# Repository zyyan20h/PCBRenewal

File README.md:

# PCB Renewal
PCB Renewal is a sustainable fabrication technique that enables renewal and reconfiguration of obsolete PCBs. This is an accompanying repository of a [research paper](https://doi.org/10.1145/3706598.3714276) published in ACM CHI 2025.

## KiCad Plugin
A plugin for the circuit design software, KiCad, that facilitates this reconfiguring process. It can be used to compare two circuit designs, crosschecking the traces and pads to figure out an efficient way to remove certain traces to transform one circuit into another.

### Installation

##### 1. Open your KiCad Plugin Directory
* You can do this by opening the PCB Editor and clicking on **Tools** > **External Plugins** > **Open Plugin Directory**
* This should open the file location where plugins are stored

##### 2. Copy plugin files into the directory
* Copy the **renewal_plugin** folder from the repository and paste it into the plugin directory
* Make sure to copy the entire folder, not just its contents

##### 3. Install Dependencies
* This plugin uses the **shapely** package
* KiCad has its own python installation, so the dependency must be intalled even if you have the package on your system's python
* Open the **KiCad 7.0 Command Prompt** (a different application from KiCad)
* type `pip install shapely` and press enter

##### 4. Check if plugin works
* Click on **Tools** > **External Plugins** > **Refresh Plugins**
* You should see the plugin show up at the right of the toolbar (the one at the top)
* Click on the plugin icon to use it

### Troubleshooting
If you don't see the plugin, make sure that you:
* Can see the plugin folder when you open the Plugin Directory
* Have installed **shapely** on *KiCad's installation of python* (see step 3)
* Have refreshed the plugins (see step 4)

One other thing you can try is using the **Python Scripting Console**
* Click the button with the terminal icon at the top of the screen
* Type `import pcbnew` and press enter
* Type `print(pcbnew.FULL_BACK_TRACE)` and press enter
* The error message should be shown on the screen
* Report the error message to the developer

### Version Information
* KiCad: 7.0.10
* Python: 3.9.16
* numpy: 1.26.1
* shapely: 2.0.4
* wxPython: 4.2.1

## Examples
Various circuit board designs that were used and reconfigured into other designs, e.g turning a PCB for a watch into one for a cat toy.

## Archive
Arudino code and old examples used during the project development.

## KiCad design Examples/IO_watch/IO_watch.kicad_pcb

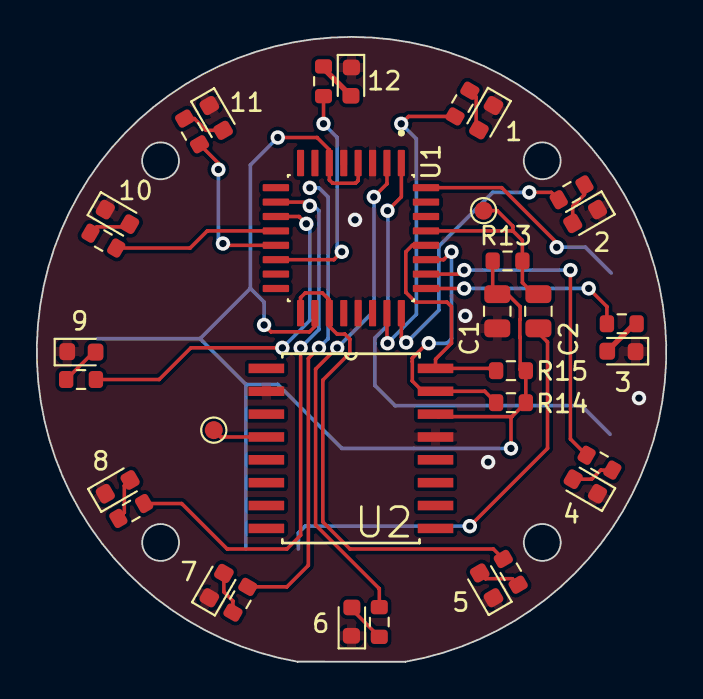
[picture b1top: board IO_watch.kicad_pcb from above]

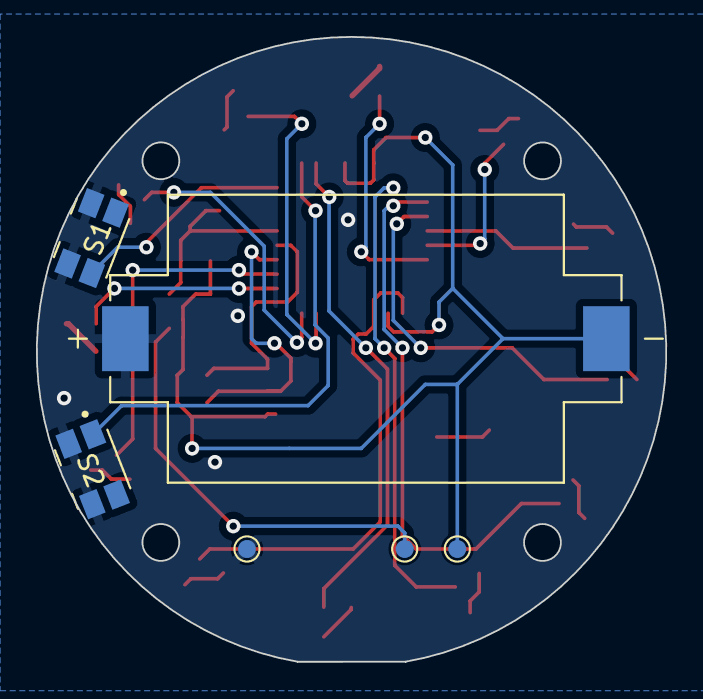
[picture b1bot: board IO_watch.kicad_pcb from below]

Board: 2 copper layers, 35.0 x 34.7 mm, 39 parts (6 on the bottom side), 33 nets.

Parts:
1, 2, 3, 4, 5, 12: LED; LED_0603_1608Metric
BT1: 1060TR; BAT_1060TR
C1: 1uF; C_0805_2012Metric
C2: 0.1uF; C_0805_2012Metric
D6, D7, D8, D9, D10, D11: LED; LED_0603_1608Metric
R1, R2, R3, R4, R5, R6, R7, R8, R9, R10, R11, R12: R; R_0603_1608Metric
R13, R14, R15: 10K; R_0603_1608Metric
S1, S2: EVQ-P7A01P; SW_EVQ-P7A01P
TP1, TP2, TP5, TP6, TP7: TestPoint; TestPoint_Pad_D1.0mm
U1: ATMEGA328P-AU; atmega328P_shinked
U2: DS3231S; DS3231

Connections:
/A0: R1.2, U1.23 (PC0)
/A1: R2.2, U1.24 (PC1)
/A2: R3.2, U1.25 (PC2)
/A3: R4.2, U1.26 (PC3)
/D2: S1.1_1, S1.1_2, U1.32 (PD2)
/D3: S2.1_1, S2.1_2, U1.1 (PD3)
/D4: R6.2, U1.2 (PD4)
/D5: R7.2, U1.9 (PD5)
/D6: R8.2, U1.10 (PD6)
/D7: R9.2, U1.11 (PD7)
/D8: R10.2, U1.12 (PB0)
/D9: R11.2, U1.13 (PB1)
/D10: R12.2, U1.14 (PB2)
/D13: R5.2, U1.17 (PB5), U1.19 (ADC6)
/D-: C2.2, TP2.1
/RST: C2.1, R13.1, TP7.1, U1.29 (PC6/~RESET)
/SCL: R15.1, U1.28 (PC5), U2.16 (SCL)
/SDA: R14.2, U1.27 (PC4), U2.15 (SDA)
GND: 1.1 (K), 2.1 (K), 3.1 (K), 4.1 (K), 5.1 (K), 12.1 (K), BT1.P, C1.2, D6.1 (K), D7.1 (K), D8.1 (K), D9.1 (K), D10.1 (K), D11.1 (K), S1.2_1, S1.2_2, S2.2_1, S2.2_2, TP5.1, U1.3 (GND), U1.5 (GND), U1.21 (GND), U2.2 (VCC), U2.13 (GND)
unnamed: 1.2 (A), R1.1
unnamed: 2.2 (A), R2.1
unnamed: 3.2 (A), R3.1
unnamed: 4.2 (A), R4.1
unnamed: 5.2 (A), R5.1
unnamed: D6.2 (A), R6.1
unnamed: D7.2 (A), R7.1
unnamed: D8.2 (A), R8.1
unnamed: D9.2 (A), R9.1
unnamed: D10.2 (A), R10.1
unnamed: D11.2 (A), R11.1
unnamed: 12.2 (A), R12.1
unnamed: TP6.1, U2.4 (~RST)
VCC: BT1.N, C1.1, R13.2, R14.1, R15.2, TP1.1, U1.4 (VCC), U1.6 (VCC), U1.18 (AVCC), U2.14 (VBAT)

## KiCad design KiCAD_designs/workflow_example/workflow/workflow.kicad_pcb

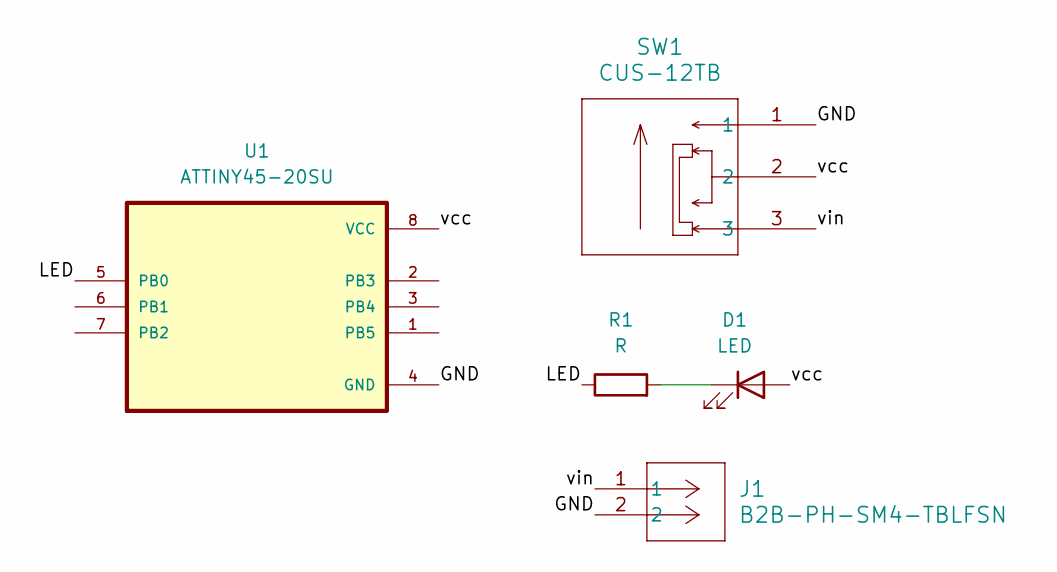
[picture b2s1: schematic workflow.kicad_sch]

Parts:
D1: LED; LED_1206_3216Metric
J1: B2B-PH-SM4-TBLFSN; B2B-PH-SM4-TBLFSN_JST
R1: R; R_0805_2012Metric
SW1: CUS-12TB; CUS-12TB_NDC
U1: ATTINY45-20SU; SOIC127P794X202-8N

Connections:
/GND: J1.2, SW1.1, U1.4 (GND)
/LED: R1.1, U1.5 (PB0)
/vcc: D1.2 (A), SW1.2, U1.8 (VCC)
/vin: J1.1, SW1.3
unnamed: D1.1 (K), R1.2

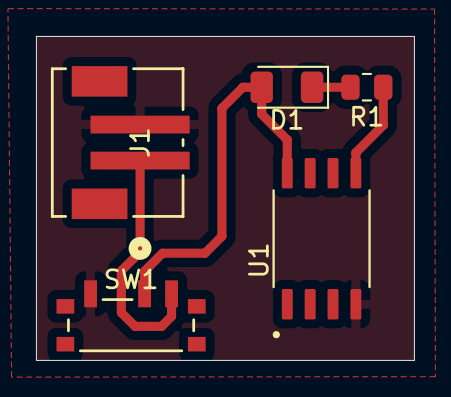
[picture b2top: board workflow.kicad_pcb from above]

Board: 2 copper layers, 21.0 x 18.0 mm, 5 parts (0 on the bottom side), 5 nets.

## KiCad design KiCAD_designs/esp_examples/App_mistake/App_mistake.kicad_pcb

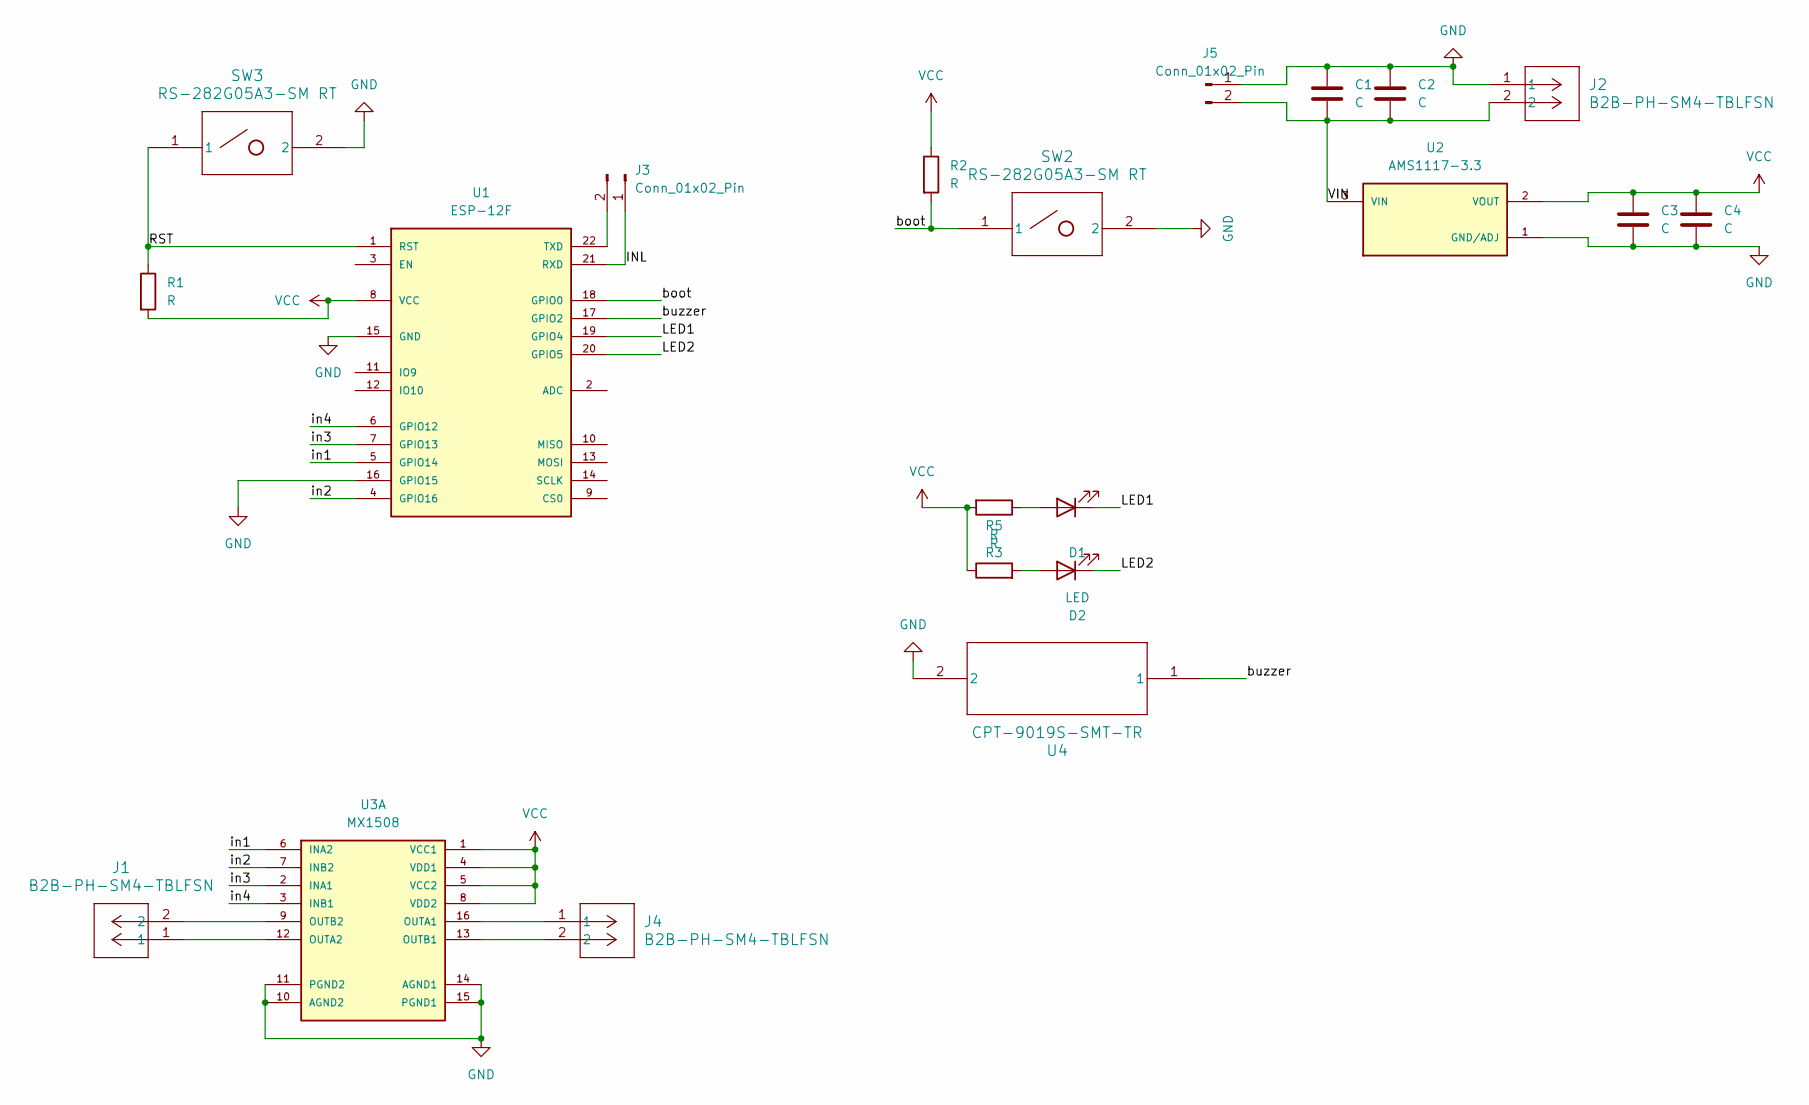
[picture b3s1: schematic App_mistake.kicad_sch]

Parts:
C1, C2, C3, C4: C; C_0805_2012Metric
D1, D2: LED; LED_1206_3216Metric
J1, J2, J4: B2B-PH-SM4-TBLFSN; B2B-PH-SM4-TBLFSN_JST
J3, J5: Conn_01x02_Pin; PinHeader_1x02_P2.54mm_Vertical
R1, R2, R3, R5: R; R_0805_2012Metric
SW2, SW3: RS-282G05A3-SM RT; RS-282G05A3-SM RT_CNK
U1: ESP-12F
U2: AMS1117-3.3; SOT229P700X180-4N
U3: MX1508
U4: CPT-9019S-SMT-TR; SM_CPT_9X9_CUD

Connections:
/INL: J3.1, U1.21 (RXD)
/LED1: D1.1 (K), U1.19 (GPIO4)
/LED2: D2.1 (K), U1.20 (GPIO5)
/RST: R1.1, SW3.1, U1.1 (RST)
/VIN: C1.2, C2.2, J2.2, J5.2, U2.3 (VIN)
/boot: R2.2, SW2.1, U1.18 (GPIO0)
/buzzer: U1.17 (GPIO2), U4.1
/in1: U1.5 (GPIO14), U3.6 (INA2)
/in2: U1.4 (GPIO16), U3.7 (INB2)
/in3: U1.7 (GPIO13), U3.2 (INA1)
/in4: U1.6 (GPIO12), U3.3 (INB1)
GND: C1.1, C2.1, C3.2, C4.2, J2.1, J5.1, SW2.2, SW3.2, U1.15 (GND), U1.16 (GPIO15), U2.1 (GND/ADJ), U3.10 (AGND2), U3.11 (PGND2), U3.14 (AGND1), U3.15 (PGND1), U4.2
unnamed: D1.2 (A), R3.1
unnamed: D2.2 (A), R5.2
unnamed: J3.2, U1.22 (TXD)
unnamed: J4.1, U3.16 (OUTA1)
unnamed: J1.1, U3.12 (OUTA2)
unnamed: J4.2, U3.13 (OUTB1)
unnamed: J1.2, U3.9 (OUTB2)
VCC: C3.1, C4.1, R1.2, R2.1, R3.2, R5.1, U1.8 (VCC), U2.2 (VOUT), U3.1 (VCC1), U3.4 (VDD1), U3.5 (VCC2), U3.8 (VDD2)

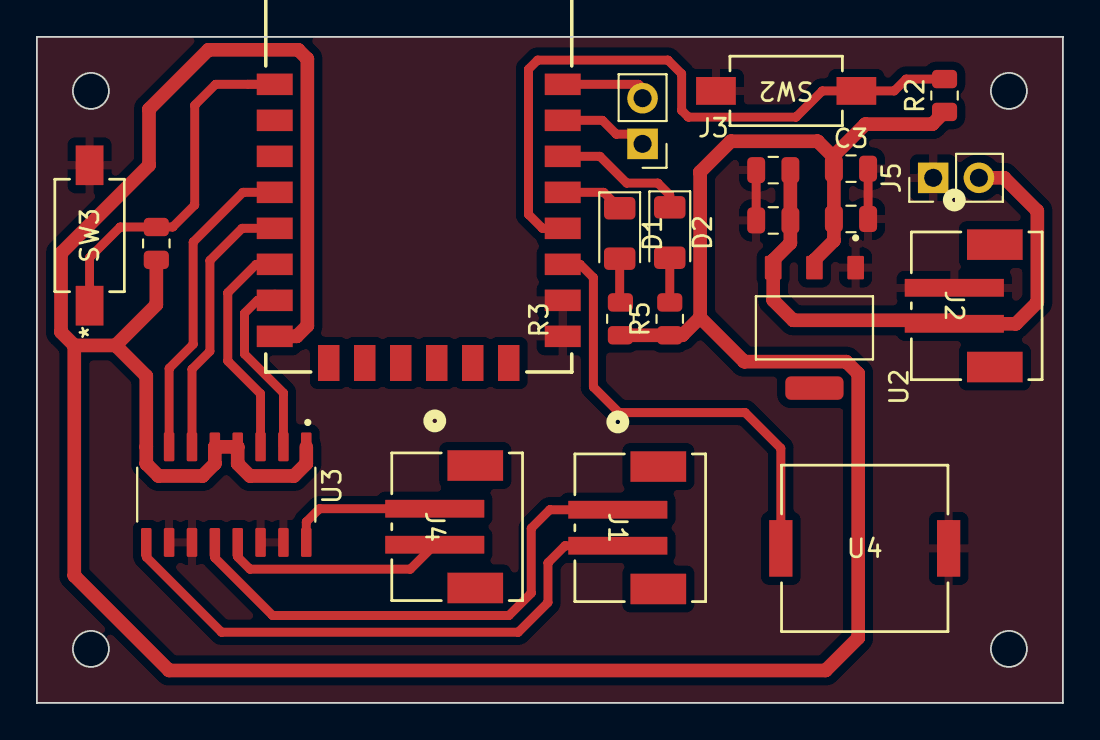
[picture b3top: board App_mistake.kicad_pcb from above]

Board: 2 copper layers, 57.0 x 37.0 mm, 21 parts (0 on the bottom side), 20 nets.

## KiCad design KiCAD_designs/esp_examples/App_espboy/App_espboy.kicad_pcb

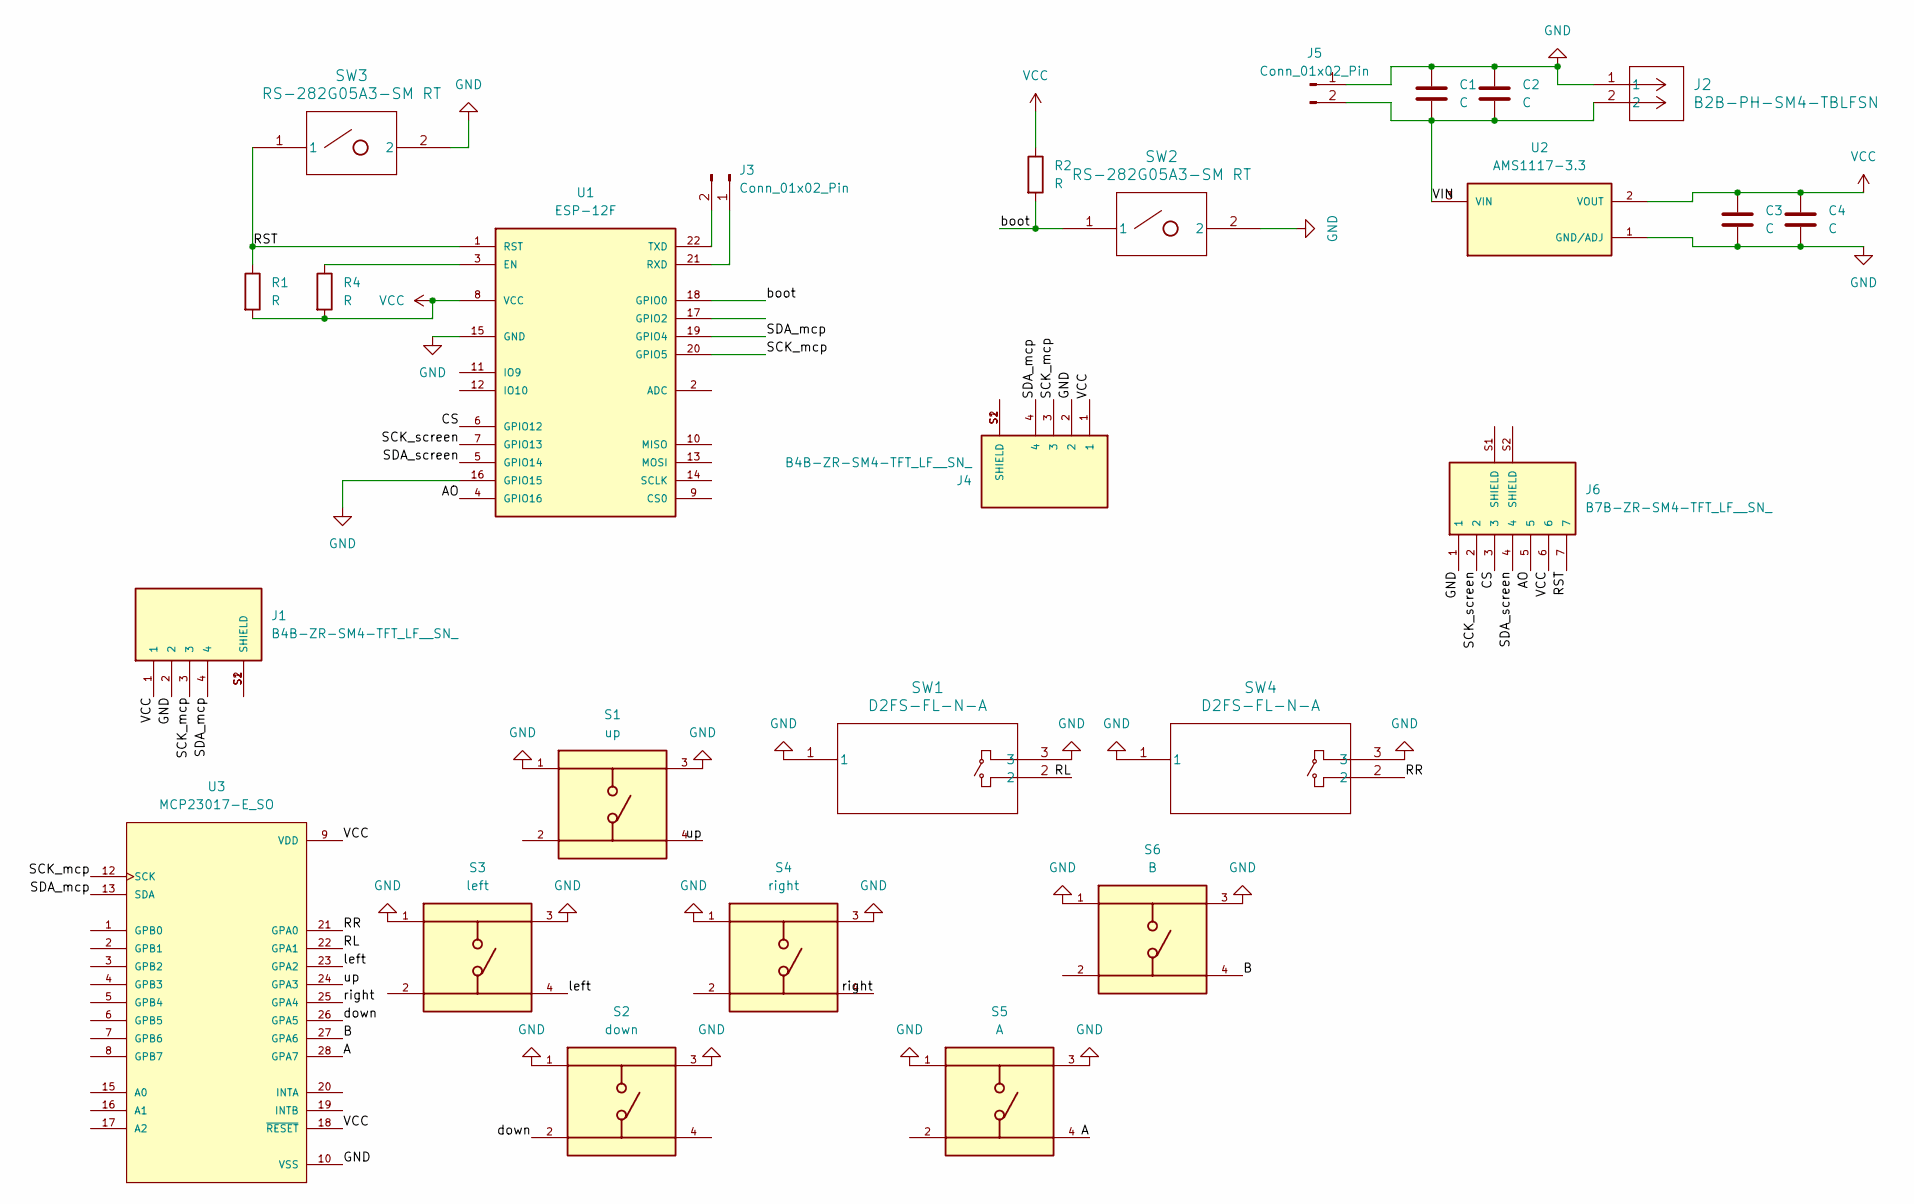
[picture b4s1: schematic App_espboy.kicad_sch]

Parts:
C1, C2, C3, C4: C; C_0805_2012Metric
J1, J4: B4B-ZR-SM4-TFT_LF__SN_; JST_B4B-ZR-SM4-TFT_LF__SN_
J2: B2B-PH-SM4-TBLFSN; B2B-PH-SM4-TBLFSN_JST
J3, J5: Conn_01x02_Pin; PinHeader_1x02_P2.54mm_Vertical
J6: B7B-ZR-SM4-TFT_LF__SN_; B7B-ZR-SM4-TBLFSN_JST
R1, R2, R4: R; R_0805_2012Metric
S1: up; switch_6
S2: down; switch_6
S3: left; switch_6
S4: right; switch_6
S5: A; switch_6
S6: B; switch_6
SW1, SW4: D2FS-FL-N-A; D2FS-FL-N-A_OMR
SW2, SW3: RS-282G05A3-SM RT; RS-282G05A3-SM RT_CNK
U1: ESP-12F
U2: AMS1117-3.3; SOT229P700X180-4N
U3: MCP23017-E_SO; MCP23017

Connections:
/A: S5.4, U3.28 (GPA7)
/AO: J6.5, U1.4 (GPIO16)
/B: S6.4, U3.27 (GPA6)
/CS: J6.3, U1.6 (GPIO12)
/RL: SW1.2, U3.22 (GPA1)
/RR: SW4.2, U3.21 (GPA0)
/RST: J6.7, R1.1, SW3.1, U1.1 (RST)
/SCK_mcp: J1.3, J4.3, U1.20 (GPIO5), U3.12 (SCK)
/SCK_screen: J6.2, U1.7 (GPIO13)
/SDA_mcp: J1.4, J4.4, U1.19 (GPIO4), U3.13 (SDA)
/SDA_screen: J6.4, U1.5 (GPIO14)
/VIN: C1.2, C2.2, J2.2, J5.2, U2.3 (VIN)
/boot: R2.2, SW2.1, U1.18 (GPIO0)
/down: S2.2, U3.26 (GPA5)
/left: S3.4, U3.23 (GPA2)
/right: S4.4, U3.25 (GPA4)
/up: S1.4, U3.24 (GPA3)
GND: C1.1, C2.1, C3.2, C4.2, J1.2, J2.1, J4.2, J5.1, J6.1, S1.1, S1.3, S2.1, S2.3, S3.1, S3.3, S4.1, S4.3, S5.1, S5.3, S6.1, S6.3, SW1.1, SW1.3, SW2.2, SW3.2, SW4.1, SW4.3, U1.15 (GND), U1.16 (GPIO15), U2.1 (GND/ADJ), U3.10 (VSS)
unnamed: J1.S1 (SHIELD), J1.S2 (SHIELD)
unnamed: J3.1, U1.21 (RXD)
unnamed: J3.2, U1.22 (TXD)
unnamed: J4.S1 (SHIELD), J4.S2 (SHIELD)
unnamed: R4.1, U1.3 (EN)
VCC: C3.1, C4.1, J1.1, J4.1, J6.6, R1.2, R2.1, R4.2, U1.8 (VCC), U2.2 (VOUT), U3.9 (VDD), U3.18 (~RESET)

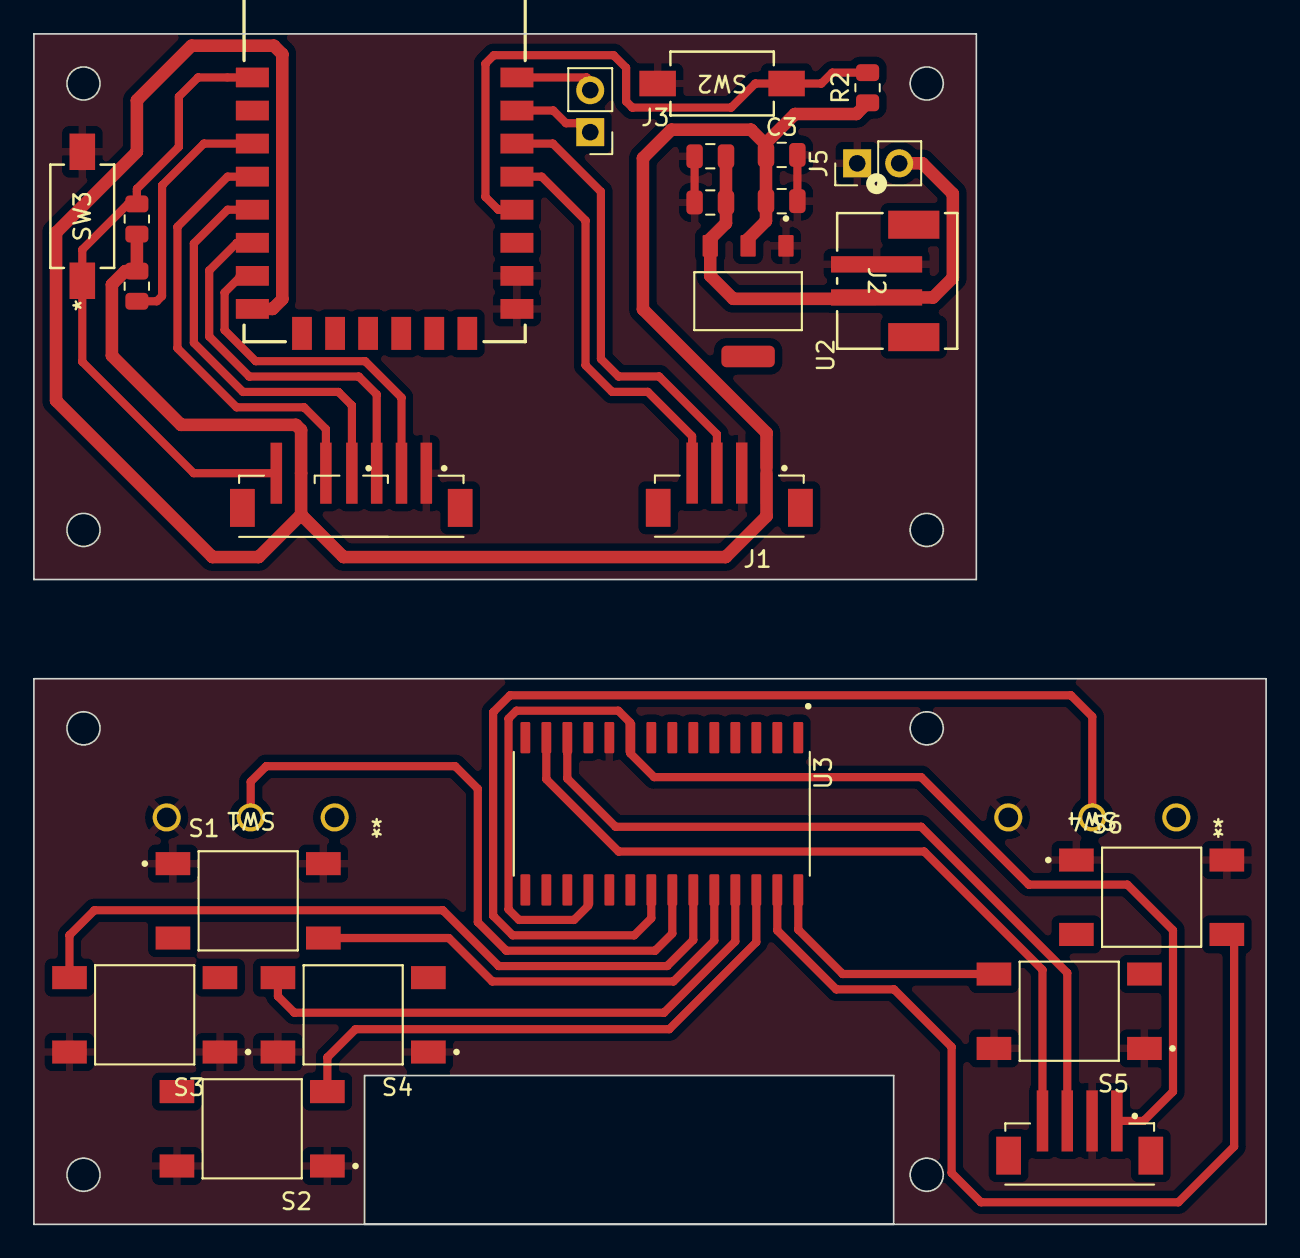
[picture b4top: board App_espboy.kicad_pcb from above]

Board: 2 copper layers, 74.5 x 72.0 mm, 26 parts (0 on the bottom side), 24 nets.

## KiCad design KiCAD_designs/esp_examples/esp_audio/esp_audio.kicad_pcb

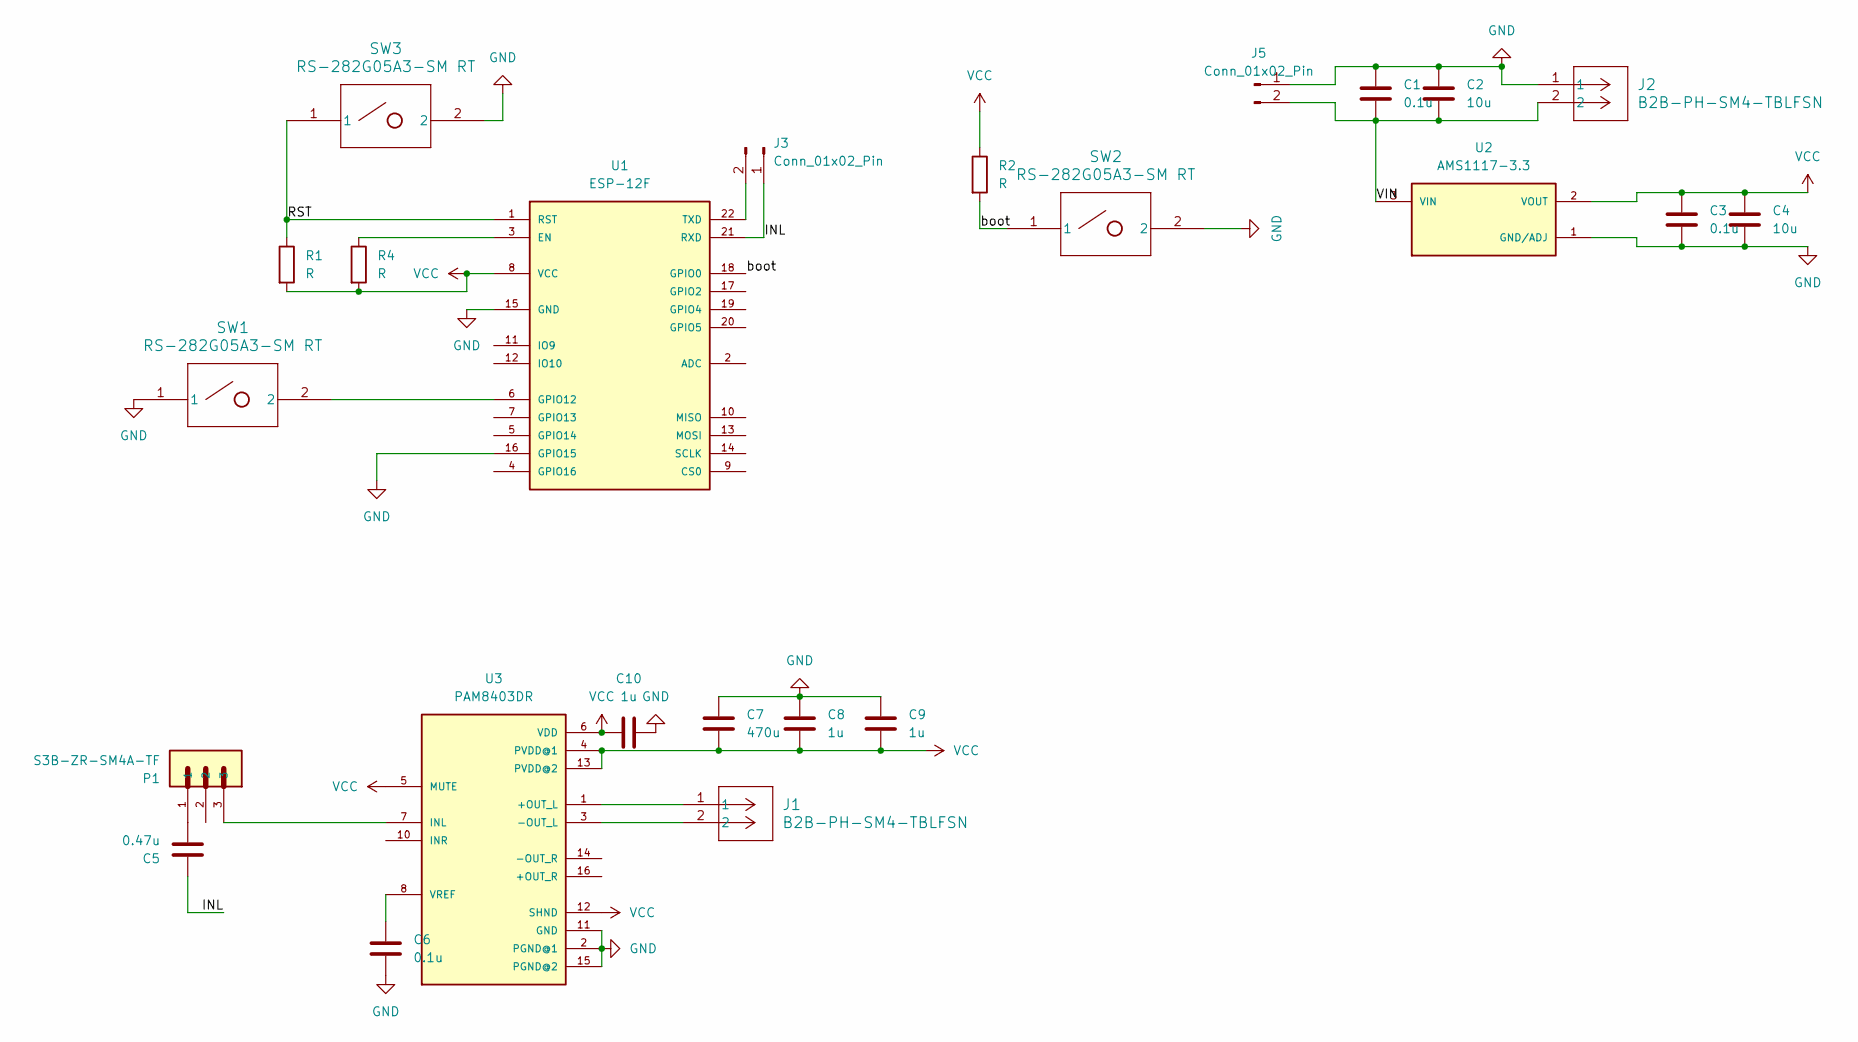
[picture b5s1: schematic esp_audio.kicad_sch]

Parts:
C1, C3, C6: 0.1u; C_0805_2012Metric
C2, C4: 10u; C_0805_2012Metric
C5: 0.47u; C_0805_2012Metric
C7: 470u; CAP_EEEFP1C471AL
C8, C9, C10: 1u; C_0805_2012Metric
J1, J2: B2B-PH-SM4-TBLFSN; B2B-PH-SM4-TBLFSN_JST
J3, J5: Conn_01x02_Pin; PinHeader_1x02_P2.54mm_Vertical
P1: S3B-ZR-SM4A-TF; JST_S3B-ZR-SM4A-TF
R1, R2, R4: R; R_0805_2012Metric
SW1, SW2, SW3: RS-282G05A3-SM RT; RS-282G05A3-SM RT_CNK
U1: ESP-12F
U2: AMS1117-3.3; SOT229P700X180-4N
U3: PAM8403DR; PAM8403

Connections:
/INL: C5.1, J3.1, U1.21 (RXD)
/RST: R1.1, SW3.1, U1.1 (RST)
/VIN: C1.2, C2.2, J2.2, J5.2, U2.3 (VIN)
/boot: R2.2, SW2.1, U1.18 (GPIO0)
GND: C1.1, C2.1, C3.2, C4.2, C6.2, C7.1, C8.1, C9.1, C10.2, J2.1, J5.1, SW1.1, SW2.2, SW3.2, U1.15 (GND), U1.16 (GPIO15), U2.1 (GND/ADJ), U3.2 (PGND@1), U3.11 (GND), U3.15 (PGND@2)
unnamed: C5.2, P1.1
unnamed: J3.2, U1.22 (TXD)
unnamed: R4.1, U1.3 (EN)
unnamed: SW1.2, U1.6 (GPIO12)
unnamed: J1.1, U3.1 (+OUT_L)
unnamed: J1.2, U3.3 (-OUT_L)
unnamed: P1.3, U3.7 (INL)
unnamed: C6.1, U3.8 (VREF)
VCC: C3.1, C4.1, C7.2, C8.2, C9.2, C10.1, R1.2, R2.1, R4.2, U1.8 (VCC), U2.2 (VOUT), U3.4 (PVDD@1), U3.5 (MUTE), U3.6 (VDD), U3.12 (SHND), U3.13 (PVDD@2)

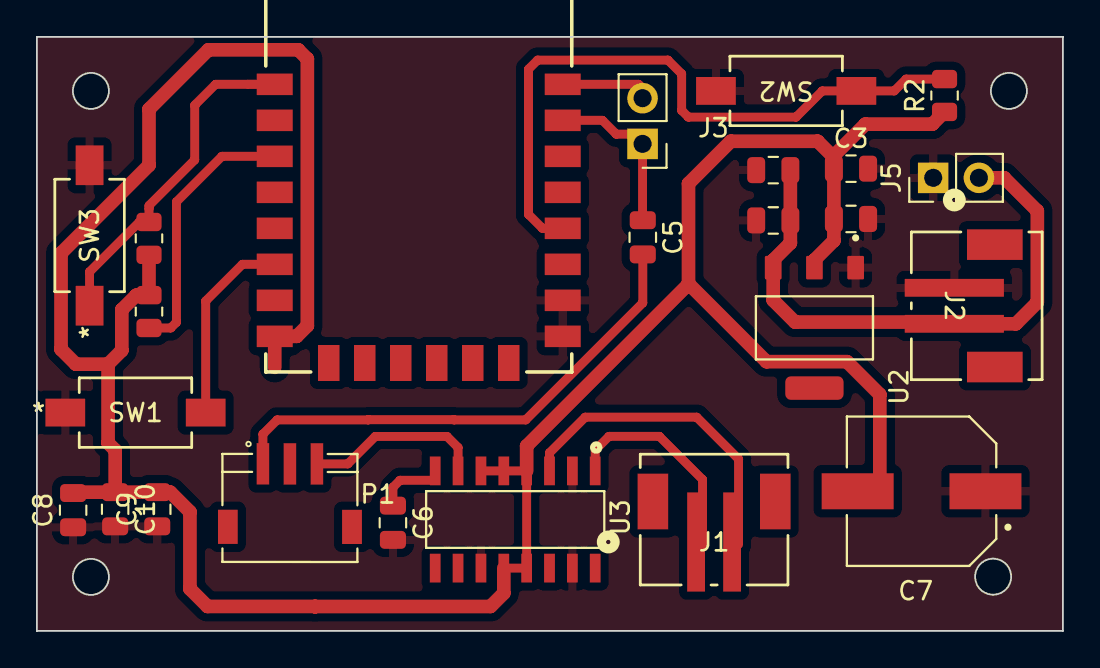
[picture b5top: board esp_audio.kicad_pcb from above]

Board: 2 copper layers, 57.0 x 33.0 mm, 24 parts (0 on the bottom side), 14 nets.

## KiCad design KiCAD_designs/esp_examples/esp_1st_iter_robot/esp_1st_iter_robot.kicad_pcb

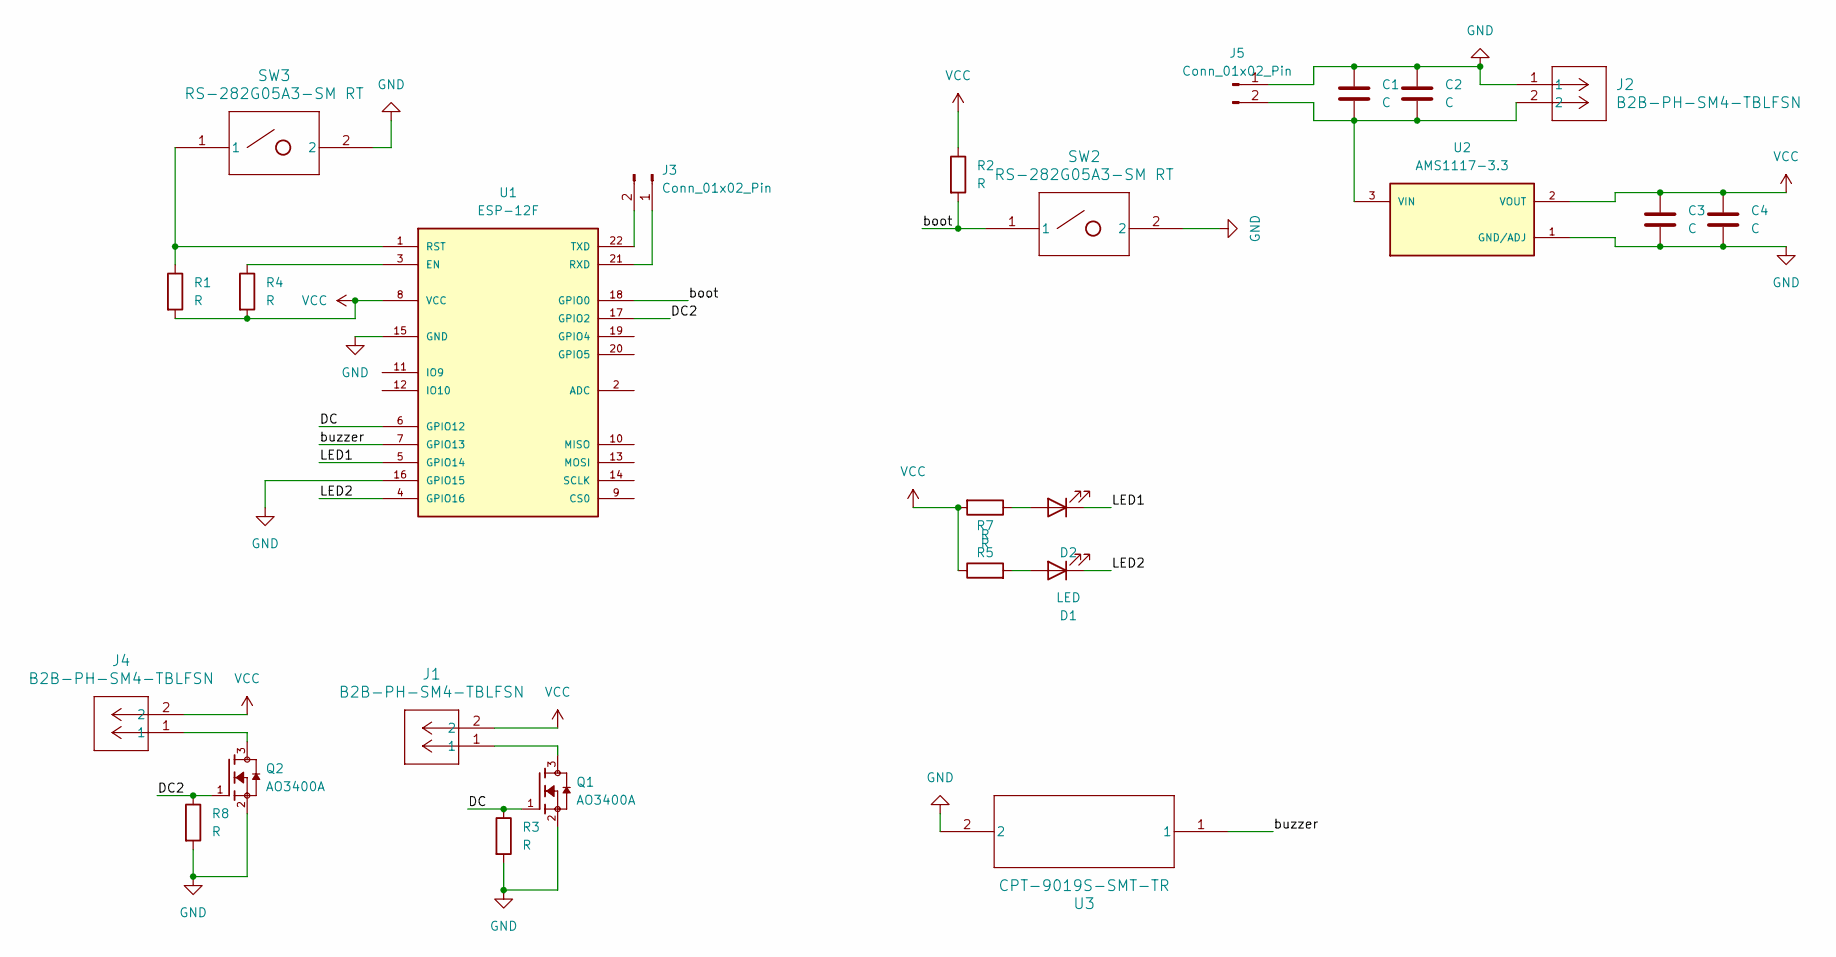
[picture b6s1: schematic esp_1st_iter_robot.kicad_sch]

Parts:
C1, C2, C3, C4: C; C_0805_2012Metric
D1, D2: LED; LED_1206_3216Metric
J1, J2, J4: B2B-PH-SM4-TBLFSN; CONN_B2B-PH-SM4-TBLFSN_JST
J3, J5: Conn_01x02_Pin; PinHeader_1x02_P2.54mm_Vertical
Q1, Q2: AO3400A; SOT95P280X125-3N; PARTREV L
R1, R2, R3, R4, R5, R7, R8: R; R_0805_2012Metric
SW2, SW3: RS-282G05A3-SM RT; RS-282G05A3-SM RT_CNK
U1: ESP-12F
U2: AMS1117-3.3; SOT229P700X180-4N
U3: CPT-9019S-SMT-TR; SM_CPT_9X9_CUD

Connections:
/DC: Q1.1, R3.1, U1.6 (GPIO12)
/DC2: Q2.1, R8.1, U1.17 (GPIO2)
/LED1: D2.1 (K), U1.5 (GPIO14)
/LED2: D1.1 (K), U1.4 (GPIO16)
/boot: R2.2, SW2.1, U1.18 (GPIO0)
/buzzer: U1.7 (GPIO13), U3.1
GND: C1.1, C2.1, C3.2, C4.2, J2.1, J5.1, Q1.2, Q2.2, R3.2, R8.2, SW2.2, SW3.2, U1.15 (GND), U1.16 (GPIO15), U2.1 (GND/ADJ), U3.2
unnamed: D1.2 (A), R7.2
unnamed: D2.2 (A), R5.1
unnamed: J1.1, Q1.3
unnamed: J3.1, U1.21 (RXD)
unnamed: J3.2, U1.22 (TXD)
unnamed: J4.1, Q2.3
unnamed: C1.2, C2.2, J2.2, J5.2, U2.3 (VIN)
unnamed: R4.1, U1.3 (EN)
unnamed: R1.1, SW3.1, U1.1 (RST)
VCC: C3.1, C4.1, J1.2, J4.2, R1.2, R2.1, R4.2, R5.2, R7.1, U1.8 (VCC), U2.2 (VOUT)

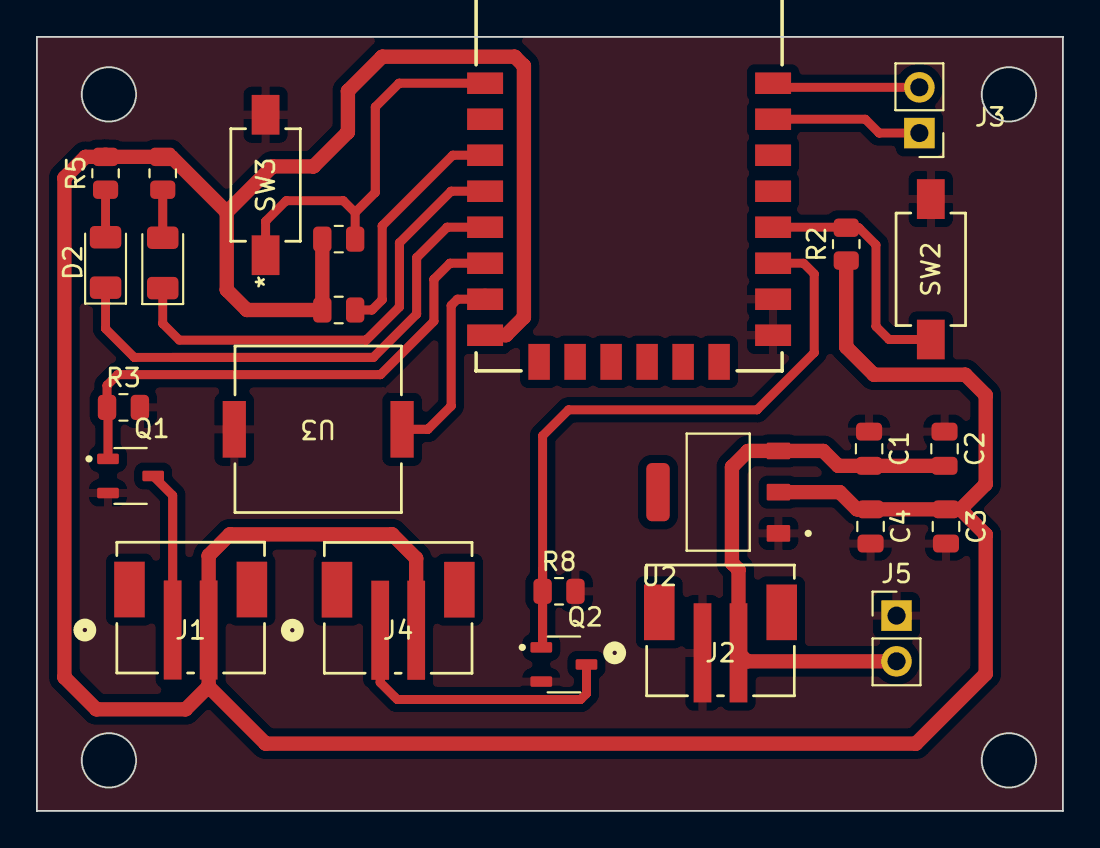
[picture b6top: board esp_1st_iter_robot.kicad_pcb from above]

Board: 2 copper layers, 57.0 x 43.0 mm, 25 parts (0 on the bottom side), 17 nets.

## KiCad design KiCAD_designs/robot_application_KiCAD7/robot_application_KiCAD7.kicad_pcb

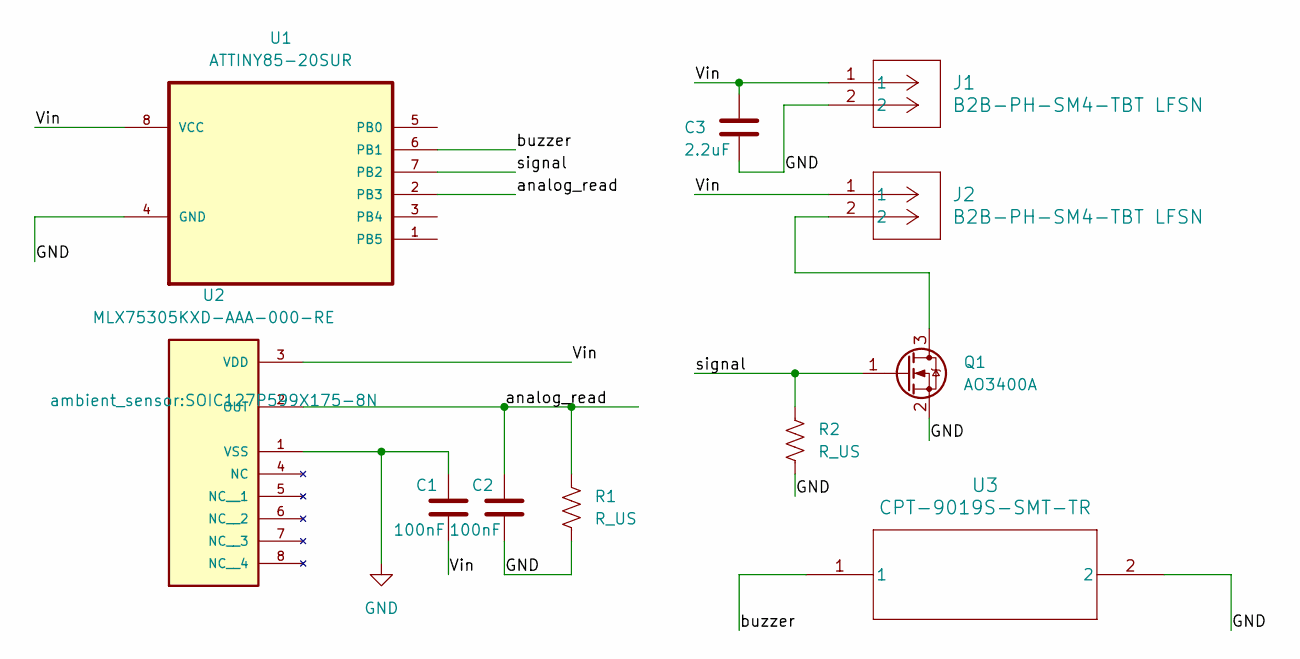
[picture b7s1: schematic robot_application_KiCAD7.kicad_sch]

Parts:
C1, C2: 100nF; C_0805_2012Metric
C3: 2.2uF; C_0805_2012Metric
J1, J2: B2B-PH-SM4-TBT LFSN; CONN2_B2B-PH-SM4_JST
Q1: AO3400A; SOT-23
R1, R2: R_US; R_0805_2012Metric
U1: ATTINY85-20SUR; MPN ATTINY85-20SUR
U2: MLX75305KXD-AAA-000-RE; SOIC127P599X175-8N; PARTREV REVISION 9 - OCTOBER 17, 2016
U3: CPT-9019S-SMT-TR; SM_CPT_9X9_CUD

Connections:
/Vin: C1.2, C3.1, J1.1, J2.1, U1.8 (VCC), U2.3 (VDD)
/analog_read: C2.1, R1.1, U1.2 (PB3), U2.2 (OUT)
/buzzer: U1.6 (PB1), U3.1
/signal: Q1.1 (G), R2.1, U1.7 (PB2)
GND: C1.1, C2.2, C3.2, J1.2, Q1.2 (S), R1.2, R2.2, U1.4 (GND), U2.1 (VSS), U3.2
unnamed: J2.2, Q1.3 (D)

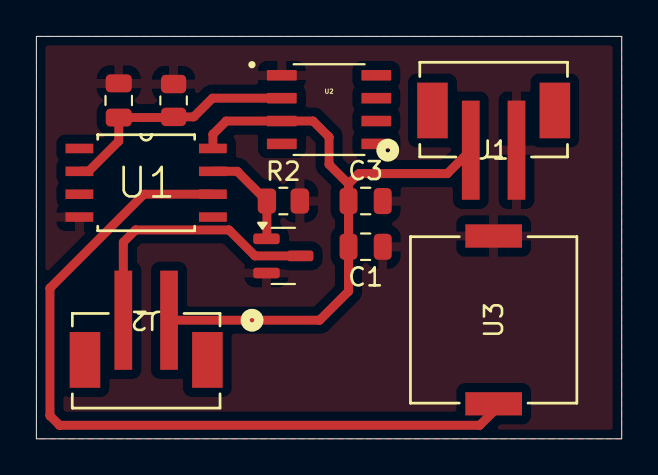
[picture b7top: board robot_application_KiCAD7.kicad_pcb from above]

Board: 2 copper layers, 32.5 x 22.4 mm, 11 parts (0 on the bottom side), 6 nets.

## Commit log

2024-01-30 project
2024-02-18 initial plugin commit
2024-02-19 plugin2-_19_24
2024-02-25 Added gerber plotting
2024-03-26 Updated UI
2024-03-26 JS_application_KiCAD_files
    Add new KiCAD files of application
2024-03-26 js_update
2024-03-26 kicad7
2024-03-28 tiny_versions
2024-03-29 esp v1
2024-03-29 esp_bot_fullRoute
2024-03-29 esp_v3_routed with keep-out
2024-03-30 all_iterations initial
2024-04-02 Made the comparison board show after pressing ok, Disabled unnecessary layers in the comparison board
2024-06-10 added svg stuff
2024-06-19 esp_camRoller
2024-06-28 Add files via upload
    8266 application code back up
2024-06-28 Added Arduino testing files. Espboy works
2024-06-29 add datasheets
2024-07-01 cs pin changed to 8266 io12
2024-07-01 cam_roller_redesign
2024-07-03 espboy_full
2024-07-03 espboy_copy
2024-07-08 add 8266 wifi radio code
2024-07-09 audio
2024-07-10 semi working version
2024-07-10 design-cleanup
2024-07-12 button changed
2024-07-12 cs pin 12, add info in README.MD
2024-07-22 Way to select components on board
2024-07-25 Added display window
2024-07-25 larger button boy
2024-07-31 23017
2024-07-31 23017 Updated
2024-08-05 fixed corner alignment
2024-08-09 cam_roller_arduino
2024-08-09 camera_roller_dynamic
2024-08-12 esp design reorg
2024-08-15 UI mistake cam_roller
2024-08-16 Made the exported svgs polygons as opposed to strokes, Layers are now ordered in the UI board visualisation, i.e. F.Cu always appears on front, the original coppers appear in front of the comparisons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
2024-08-16 Removed references to the selection dialog, because it was removed and is causing errors
2024-08-20 offset to 0.45
2024-08-20 workflow example
2024-08-22 Exporting edge cut difference, overwrite stuff
2024-08-22 js 0822
2024-08-26 Fixed bug where edge cuts weren't properly compared after alignment. Made the comparison take into account the current alignment offset
2024-08-26 The components and edge cuts were misaligned when exporting whenever they were aligned for comparison. I offset the components by the alignment offset as well.
2024-08-28 tiles
2024-09-03 implemented the sustainability calculations save for the fr4 material ones. Also I'm using a fixed path length instead of getting it
2024-09-04 added sustainability calculation for fiberglass and copper
2024-09-06 Added functionality to save parameters to the configuration file
2024-09-07 Added labels for the multiple choice boxes in the ALign Boards section
2024-09-08 Made the board visualisation take up the entire right half of the screen
2024-09-08 misalign
2024-09-08 Fixed bug where the edge cuts weren't aligned after comparison
2024-09-10 updated the formulas
2024-09-10 Added ceiling functions to time formulas. Removed comparison method selection and export original board checkbox
2024-09-10 Addeed extra stuff to sustainability evaluation
2024-09-11 fixed some of the sustainability formulas
2024-09-11 calculation final
2024-09-11 Made default sustainability params match the ones in the config file. Labeled the comparison results in the layer controls of the board visualisation
2024-11-11 double layer examples
2024-11-18 ordered
2024-11-22 Added support for vias
2024-11-24 Made pads takes their layer from their parent footprint
2024-12-02 Added 0.1 offset to diameter of drilled out vias
2024-12-02 fixed type error in previous commit
2024-12-03 changed cat ball via size
2024-12-03 Exported edge cuts gerber now includes vias present on the new board and not on the old board as well
2024-12-05 Stopped units from rounding to integers when converting to svg
2024-12-05 catball thicker traces
2024-12-06 .\second_plugin\
2024-12-06 Added warnings and fixed colours
2024-12-10 added a message letting you knwo about warnings and adjusted how much the log scrolls down
2025-02-12 Renamed folders, Created an archive folder, moved old examples to it. Removed old commented out code, and commented out debug print statements. Added version info to the plugin readme
2025-02-12 Made it so there's only 1 readme
